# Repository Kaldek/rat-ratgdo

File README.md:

# rat-ratgdo
RAGE
AGAINST
THE
RATGDO

Credit and inspiration for this work goes to [@rlowens](https://github.com/rlowens) to let me know that there are other technical folks out there who needed this other than myself.

## Overview
This is an open source schematic for the ratgdo, based on the v2.5 [ratgdo](https://github.com/PaulWieland/ratgdo) PCB and code but installed using the [ESPHome fork](ESPHome%20vs%20native%20ratgdo.md) of ratgdo.  This project was created to allow people who need a ratgdo solution for their garage door opener but either cannot, or choose not to, source the solution from Paul Wieland. It also ensures that the PCB can be recreated as and when the project maintainer gives up on the project (much like Chamberlain themselves might do with their MyQ Cloud Service) and stops selling PCBs. 

### You are expected to know how to create the described circuit using your own prototyping skills.  That is, this project is for people who can solder well and know how to read schematics

The ***basic*** PCB schematic shown here in the Readme does not describe any circuitry other than the serial line garage door control and obstruction sensor.  All other optional features provided by ratgdo can be reverse engineered as needed, or may already be solved by one of the schematics the community has uploaded!

 As of January 2023, there are now multiple sources for commercially sold ratgdo boards.  **However if you want to buy a pre-made ratgdo setup, we recommend purchasing one [from Paul Wieland](https://github.com/PaulWieland/ratgdo) so as to reward the original creator.**

_Simple basic schematic for a Wemos D1 Mini based module_

See images of a [working breadboard prototype](images/Breadboard_working.png) and the [subsequent soldered prototype using a D1 shield](images/Simple%20prototype%20using%20D1%20shield.jpg).  Both of these prototypes are using 2n7000 MOSFETs exclusively, but that is because they are prototypes and whether a 2n7000 will work for TX will depend greatly on who manufactured your 2n7000.  See the section below on needed components for context.

## Components needed for basic functionality
The basic schematic shown above assumes the use of through-hole components.  If you wish to use SMD components, please refer to the [FAQ](FAQ.md#what-if-i-want-to-use-sot-23-smd-components), and you can also check out the community-provided schematics, which include SMD-based designs.

For this basic design, aside from the obvious requirement of a [supported ESP-32 or ESP8266 board](Supported%20Boards.md) flashed with the [ESPHome version](https://github.com/ratgdo/esphome-ratgdo), you will need:
- 3x 10 kohm (kilo-ohm) resistors
- 1x 2n7000 MOSFET for the RX pin
- 1x AO3400A (soldered to a SOT23 to DIP adapter board) for the TX pin.

It is also recommended you aquire a suitable 3-post screw terminal and some red, white, and black wire for connecting to the door opener.  These connections are very low current, so you can get away with fairly thin wire.

**Note:**  You may **try** to use a 2n7000 MOSFETs for **both** RX and TX, however depending on the manufacturere of your 2n7000 and its production batch, it might not be 100% reliable for the TX circuit because the ~3v switching signal from the ESP8266 may not be enough to trigger the gate of the 2n7000.  There are many examples working using the 2n7000 however, so it might work.  If you have reliability issues for sending commands, we can only recommend you use the AO3400A SMD MOSFET, soldered to a SOT23-to-DIP adapter board.  

## INSTALL REQUIREMENTS
For both this basic schematic shown here in the Readme and how they it is laid out, you must use the ESPHome fork of ratgdo and - for ESP8266 based boards - select the "ratgdo v2.5x" image on the ESPhome [web installer page](https://ratgdo.github.io/esphome-ratgdo/).  For ESP32 based boards the above does not currently apply and you must use the v2.0 installer and follow our basic ESP-32 schematic we provide in the Supported Boards page.

For the ESP8266 based boards, if installing using Paul Wieland's native ratgdo installer and you install for a v2.0 board, you must wire your TX to D4 (GPIO2) rather than D1 (GPIO5).

## Having a PCB printed
You may use the files from the [schematics folder](kicad_files) to have your own PCB printed.  Shown is an example 3D render of an ESP32 based board using a Wemos ESP32 D1 board.

_An example of the D1 Mini ESP32 Wide Format_

Here is an example of a printed PCB with a raw ESP8266 and an LM2596 module, for being powered by a GDO with the battery backup capabilities.

_An example of a PCB using a bare ESP8266 and LM2596 module_

### Schematic options
The community has provided a few options of schematic files suitable for sending to a PCB printing company.
- [Wemos D1 Mini ESP8266](kicad_files/D1%20Mini%20-%20ESP8266)
- [Wemos D1 Mini ESP32](kicad_files/D1%20Mini%20-%20ESP32) (massive overkill for ratgdo but it's your choice!)
- [Wemos D1 Mini ESP32 Wide Format](kicad_files/D1%20Mini%20Wide%20-%20ESP32)
- [Bare ESP8266 module](kicad_files/Bare%20ESP8266)

> If you just want to try ordering a board from somewhere like PCBWay, then check out the most recent [build artifacts](https://github.com/Kaldek/rat-ratgdo/actions/workflows/pcb.yaml)

## How the ratgdo circuit works
The ratgdo circuitry which we cover in this project consists of two sections; Garage Door control and obstruction sensors.

### Garage Door Control
#### Description of the Chamberlain configuration
The Chamberlain garage door control circuit is a two-wire setup consisting of a Ground, and a combined +12v power and serial data line.  The serial data line is held at 12v unless data transmission is occurring.  Data transmission is performed by pulling the 12v line down to GND for each data bit.  The benefit here is that a single wire can be used for providing power to door control panels and data transmssion on a single wire.  The use of appropriately sized capacitors in door control panels means they do not switch off during data transmission.

#### How ratgdo interfaces with the Chamberlain wiring
The ratgdo taps into the red control wire and uses this single wire for transmission of commands onto the serial bus, and for receiving data from the serial bus.  As it is a single wire protocol and operates half-duplex, the ratgdo circuitry uses N-channel MOSFETs wired in a manner which allows the ESP8266 to never transmit when the serial line is already low.

In operation, this means that the ratgdo is mostly listening to the serial bus to ensure it is keeping track of the state of the door.  For example, if the door is manually opened (or opened by use of the MyQ app even), these events are broadcast onto the serial bus by the door controller.  ratgdo is therefore able to know that the state of the door has changed.  In turn, this means that when controlling ratgdo via Home Assistant, the status of the door in HA is always up to date.

#### Wiring to Garage Door

### Obstruction sensor
The ratgdo monitors the real-time state of the obstruction sensors directly.  We assume this is because obstruction status is not broadcast in real time by the door controller, and safety is paramount.  It allows you to set up real-time alerts in Home Assistant for any time the door is obstructed.  The ratgdo taps into the obstruction sensor power wire which also acts as a communication bus, however the signalling is only an ongoing status of whether the obstruction sensors are working and whether there is an obstruction.

## Contributing
This is a fully open repo, in that we welcome any and all additions for all sorts of Edge Cases.  If you come up with something and would like it to be available to the community, raise a Pull Request and we'll work with you to get it published!

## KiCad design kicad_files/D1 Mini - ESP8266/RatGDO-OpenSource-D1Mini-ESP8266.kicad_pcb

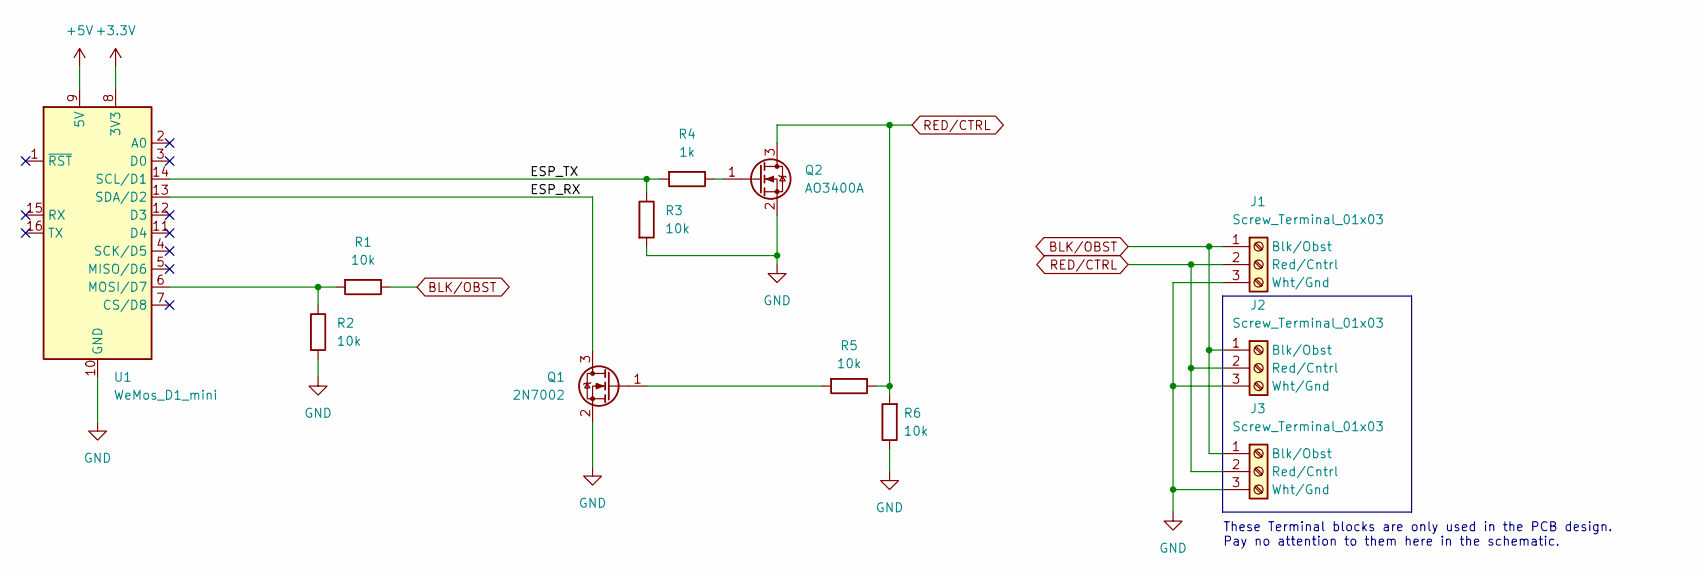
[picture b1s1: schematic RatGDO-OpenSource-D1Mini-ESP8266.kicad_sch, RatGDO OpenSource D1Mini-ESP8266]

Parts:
J1: Screw_Terminal_01x03; TerminalBlock_Phoenix_MKDS-1,5-3_1x03_P5.00mm_Horizontal
J2: Screw_Terminal_01x03; PhoenixContact_MCV_1,5_3-G-3.5_1x03_P3.50mm_Vertical
J3: Screw_Terminal_01x03; PinHeader_1x03_P2.54mm_Vertical
Q1: 2N7002; SOT-23_Handsoldering
Q2: AO3400A; SOT-23_Handsoldering
R1, R2, R3, R5, R6: 10k; R_0805_2012Metric_Pad1.20x1.40mm_HandSolder
R4: 1k; R_0805_2012Metric_Pad1.20x1.40mm_HandSolder
U1: WeMos_D1_mini; WEMOS_D1_mini_light

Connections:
+3.3V: U1.8 (3V3)
+5V: U1.9 (5V)
/ESP_RX: Q1.3 (D), U1.13 (SDA/D2)
/ESP_TX: R3.1, R4.2, U1.14 (SCL/D1)
BLK/OBST: J1.1 (Blk/Obst), J2.1 (Blk/Obst), J3.1 (Blk/Obst), R1.1
GND: J1.3 (Wht/Gnd), J2.3 (Wht/Gnd), J3.3 (Wht/Gnd), Q1.2 (S), Q2.2 (S), R2.2, R3.2, R6.1, U1.10 (GND)
unnamed: Q1.1 (G), R5.2
unnamed: Q2.1 (G), R4.1
unnamed: R1.2, R2.1, U1.6 (MOSI/D7)
RED/CTRL: J1.2 (Red/Cntrl), J2.2 (Red/Cntrl), J3.2 (Red/Cntrl), Q2.3 (D), R5.1, R6.2

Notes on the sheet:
These Terminal blocks are only used in the PCB design. Pay no attention to them here in the schematic.

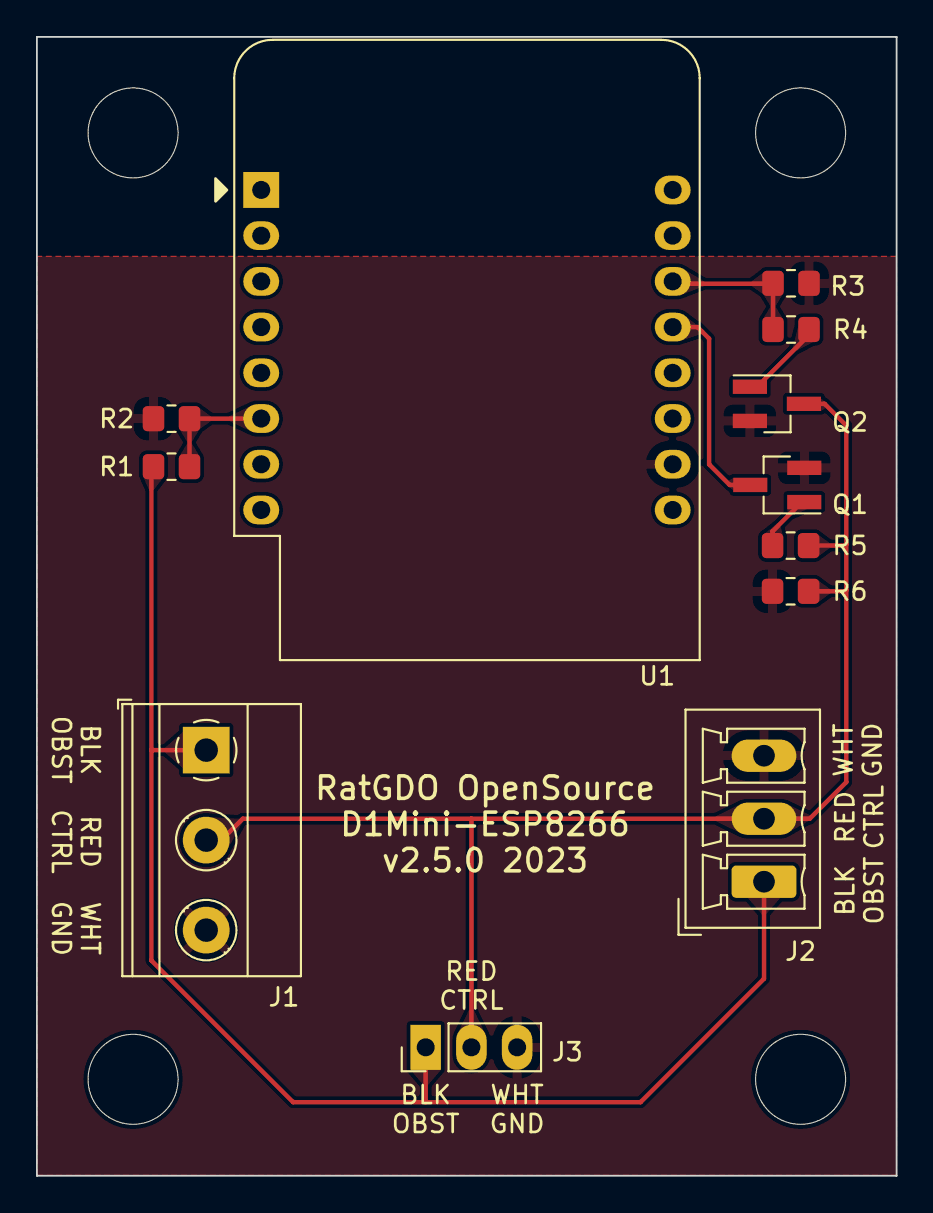
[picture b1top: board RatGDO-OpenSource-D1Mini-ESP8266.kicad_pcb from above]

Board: 2 copper layers, 47.8 x 63.3 mm, 16 parts (0 on the bottom side), 8 nets.

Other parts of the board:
H1, H1#2, H1#3, H1#4: MountingHole_5mm

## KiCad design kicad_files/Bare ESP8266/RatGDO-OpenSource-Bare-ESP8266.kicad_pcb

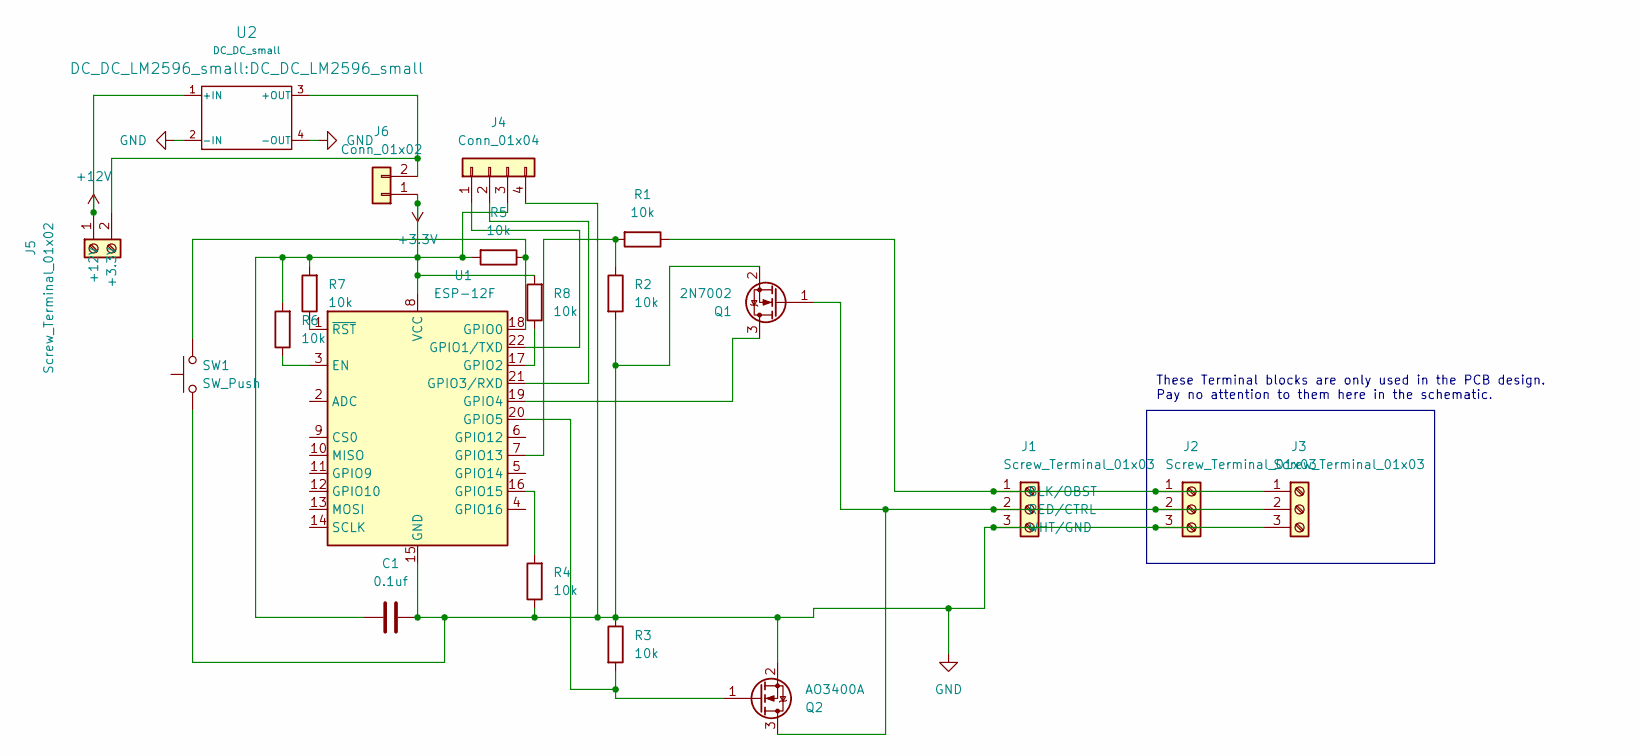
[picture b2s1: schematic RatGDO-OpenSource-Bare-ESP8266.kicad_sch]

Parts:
C1: 0.1uf; C_0805_2012Metric
J1: Screw_Terminal_01x03; TerminalBlock_Phoenix_MKDS-1,5-3_1x03_P5.00mm_Horizontal
J2: Screw_Terminal_01x03; PhoenixContact_MCV_1,5_3-G-3.5_1x03_P3.50mm_Vertical
J3: Screw_Terminal_01x03; PinSocket_1x03_P2.54mm_Vertical
J4: Conn_01x04; PinSocket_1x04_P2.54mm_Vertical
J5: Screw_Terminal_01x02; TerminalBlock_Phoenix_MKDS-1,5-2_1x02_P5.00mm_Horizontal
J6: Conn_01x02; PinHeader_1x02_P2.54mm_Vertical
Q1: 2N7002; SOT-23
Q2: AO3400A; SOT-23
R1, R2, R3, R4, R5, R6, R7, R8: 10k; R_0805_2012Metric
SW1: SW_Push; SW_SPST_EVQQ2
U1: ESP-12F; ESP-12E
U2: DC_DC_small; DC_DC_LM2596_small

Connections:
+3.3V: C1.1, J4.3, J6.1, R5.2, R6.2, R7.2, R8.2, U1.8 (VCC)
+12V: J5.1 (+12V), U2.1 (+IN)
GND: C1.2, J1.3 (WHT/GND), J2.3, J3.3, J4.4, Q1.2 (S), Q2.2 (S), R2.2, R3.1, R4.1, SW1.1, U1.15 (GND), U2.2 (-IN), U2.4 (-OUT)
unnamed: J1.1 (BLK/OBST), J2.1, J3.1, R1.1
unnamed: J1.2 (RED/CTRL), J2.2, J3.2, Q1.1 (G), Q2.3 (D)
unnamed: J4.1, U1.22 (GPIO1/TXD)
unnamed: J4.2, U1.21 (GPIO3/RXD)
unnamed: J5.2 (+3.3V), J6.2, U2.3 (+OUT)
unnamed: Q1.3 (D), U1.19 (GPIO4)
unnamed: Q2.1 (G), R3.2, U1.20 (GPIO5)
unnamed: R6.1, U1.3 (EN)
unnamed: R5.1, SW1.2, U1.18 (GPIO0)
unnamed: R8.1, U1.17 (GPIO2)
unnamed: R1.2, R2.1, U1.7 (GPIO13)
unnamed: R4.2, U1.16 (GPIO15)
unnamed: R7.1, U1.1 (~RST)

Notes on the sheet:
These Terminal blocks are only used in the PCB design. Pay no attention to them here in the schematic.

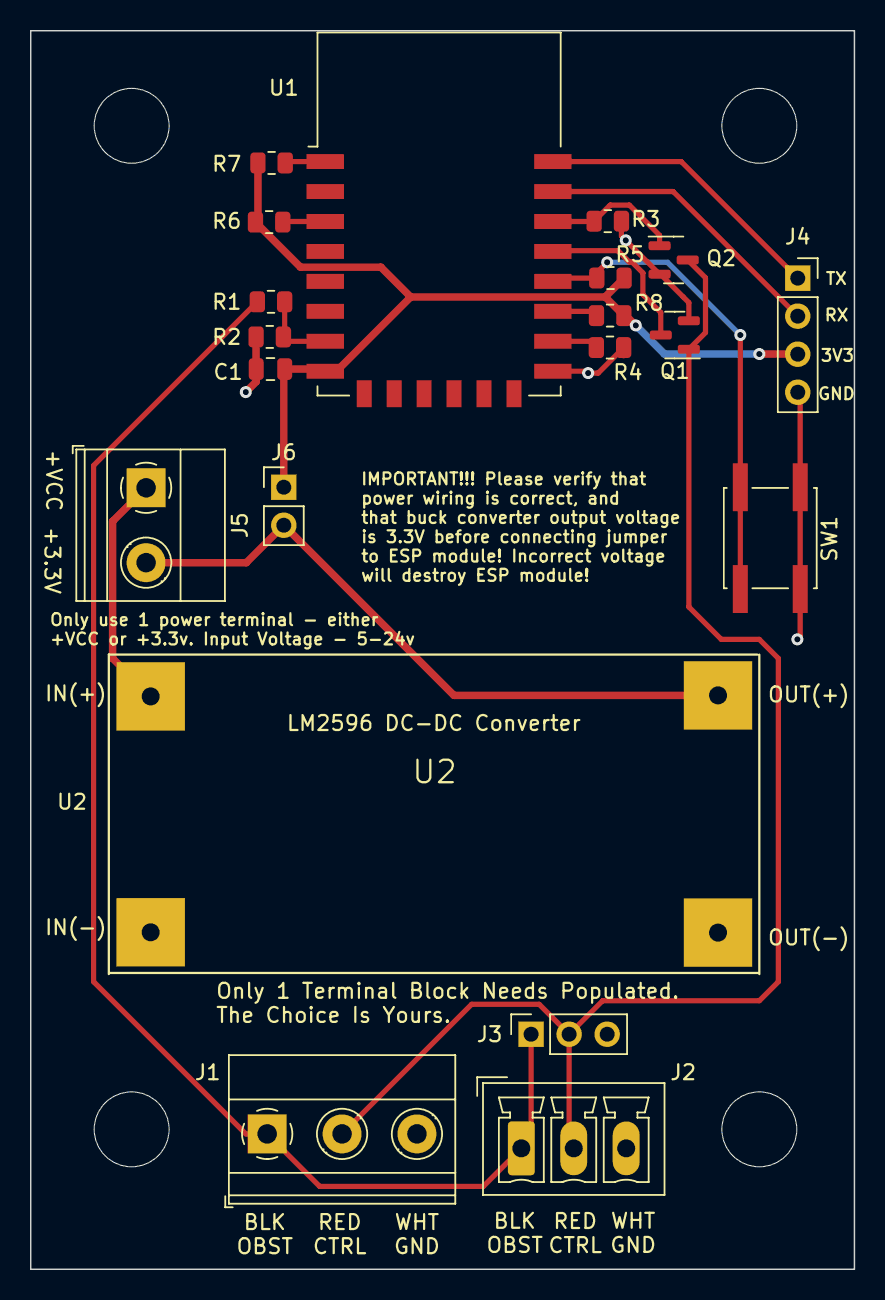
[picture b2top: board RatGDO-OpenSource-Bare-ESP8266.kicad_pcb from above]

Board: 2 copper layers, 55.0 x 82.7 mm, 24 parts (0 on the bottom side), 16 nets.

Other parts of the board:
H1, H1#2, H1#3, H1#4: MountingHole_5mm

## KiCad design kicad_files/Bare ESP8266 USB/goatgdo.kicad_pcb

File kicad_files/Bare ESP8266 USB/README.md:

# ESP8266 12-F USB-C KiCad files

A reworking of the Bare ESP8266 board design that uses USB-C for power instead of an LM2596 submodule, and uses just one GDO connector header to allow for a smaller board footprint.

Compatable with RatGDO ESPHome software for the v2.5 official board.

## Populating

Populating the Flash switch, Reset switch, and ICSP header are optional, but will make first time programming easier.

## Powering 

This board uses a 6-pin power-only USB-C jack that can be either hand soldered or paste reflowed. It's a normal 5V USB sink device, so any "dumb" USB wall-wart can be used.

It can also be powered via the 3.3V pin of the ICSP header - there's no need to connect USB while serial programming it.

If you wish to power the device directly from the programming header using 3.3V, you can skip populating the USB-C port, resistors R2 and R3, and the LDO regulator CR1, but you should ensure you're using a stable and regulated 3.3V supply.

If your GDO has battery backup system, I'd recommend using one of the LM2996 module based boards in this repository instead of this one.

## Programming

The USB-C port on this board is for power only - you need to use the ICSP programming header with a seperate TTL-level RS232 programming interface to load the initial firmware.

The ICSP header will mate directly with the 
[SparkFun Serial Basic Breakout](https://www.sparkfun.com/products/14050) for programming, but any 3.3V RS232 interface can be used by connecting TX, RX, VCC and GND appropriately.

Auto reset via serial hardware control lines isn't supported - you'll need to press the Reset button manually after programming, or power cycle the device.

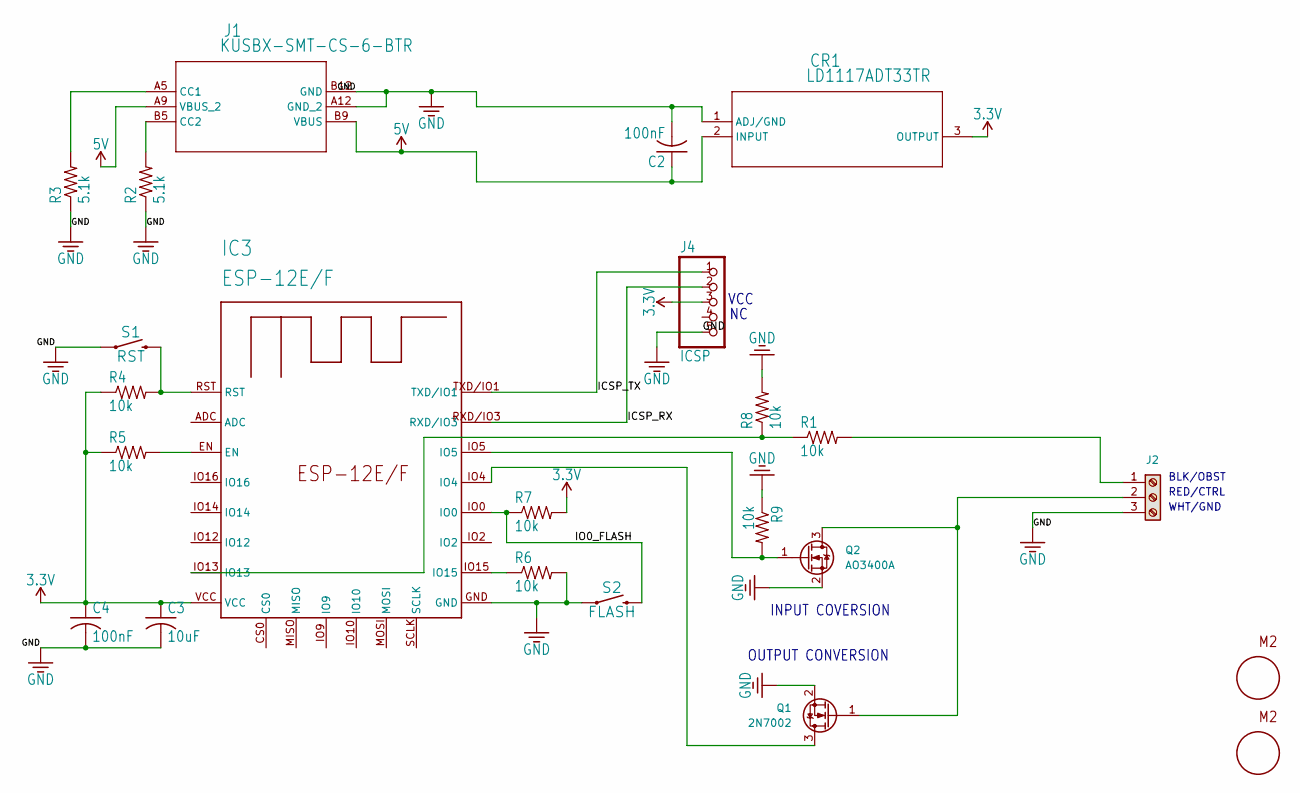
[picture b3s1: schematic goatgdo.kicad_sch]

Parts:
C2, C4: 100nF; C0805
C3: 10uF; C0805
CR1: LD1117ADT33TR; DPAK_STM
IC3: ESP-12E/F; ESP-12E
J1: KUSBX-SMT-CS-6-BTR; KUSBX-SMT-CS-6-BTR_KYC
J2: Screw_Terminal_01x03; TerminalBlock_MetzConnect_Type011_RT05503HBWC_1x03_P5.00mm_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
J4: ICSP; 1X05
Q1: 2N7002; SOT-23_Handsoldering
Q2: AO3400A; SOT-23_Handsoldering
R1, R4, R5, R6, R7, R8, R9: 10k; R0805
R2, R3: 5.1k; R0805
S1: RST; TACTILE_SWITCH_PTH_6.0MM
S2: FLASH; TACTILE_SWITCH_PTH_6.0MM
U$4, U$6: M2-POST

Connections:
3.3V: C3.1, C4.1, CR1.3 (OUTPUT), IC3.VCC, J4.3, R4.1, R5.1, R7.2
5V: C2.1, CR1.2 (INPUT), J1.A9 (VBUS_2), J1.B9 (VBUS)
/ICSP_RX: IC3.RXD/IO3, J4.2
/ICSP_TX: IC3.TXD/IO1, J4.1
/IO0_FLASH: IC3.IO0, R7.1, S2.3 (2)
GND: C2.2, C3.2, C4.2, CR1.1 (ADJ/GND), IC3.GND, J1.A12 (GND_2), J1.B12 (GND), J2.3, J4.5, Q1.2 (S), Q2.2 (S), R2.1, R3.1, R6.2, R8.2, R9.1, S1.1, S2.1
unnamed: IC3.EN, R5.2
unnamed: IC3.IO13, R1.1, R8.1
unnamed: IC3.IO15, R6.1
unnamed: J1.A5 (CC1), R3.2
unnamed: J1.B5 (CC2), R2.2
unnamed: J2.1, R1.2
unnamed: J2.2, Q1.1 (G), Q2.3 (D)
unnamed: IC3.IO4, Q1.3 (D)
unnamed: IC3.IO5, Q2.1 (G), R9.2
unnamed: IC3.RST, R4.2, S1.3 (2)

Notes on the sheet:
INPUT COVERSION
BLK/OBST
WHT/GND
OUTPUT CONVERSION
RED/CTRL
VCC

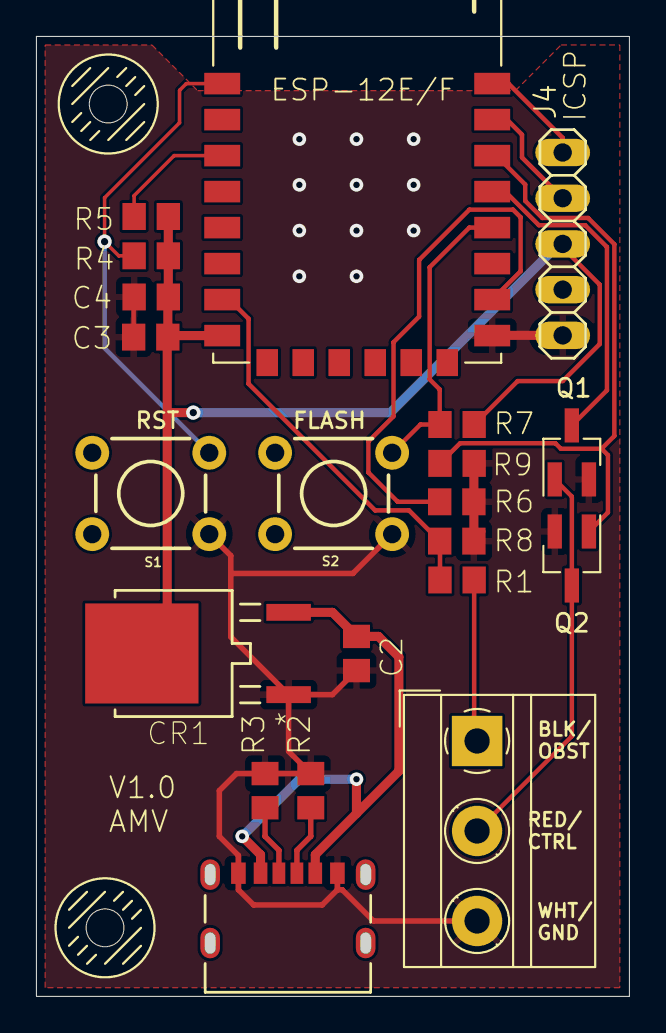
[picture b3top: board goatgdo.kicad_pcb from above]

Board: 2 copper layers, 32.4 x 52.8 mm, 23 parts (0 on the bottom side), 16 nets.

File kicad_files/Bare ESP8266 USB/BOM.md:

## BOM

|Part 	|Qty 	|Value 	|Reference 	|Link 	|
|-|-|-|-|-|
|0805 Resistor 				|7 	|10k 	|R1, R4, R5, R6, R7, R8, R9 	|																											|
|0805 Resistor 				|2 	|5.1k 	|R2, R3 						|																											|
|0805 Capacitor				|2 	|100nF 	|C2, C4 						|																											|
|0805 Capacitor				|1 	|10uF	|C3 							| 																											|
|Switch (Optinal) 			|2 	| 		|S1 (Rst), S2 (Flash)			|[Digikey](https://www.digikey.com/en/products/detail/cui-devices/TS02-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 		|
|2N7002 					|1 	| 		|Q1 							|[Digikey](https://www.digikey.com/en/products/detail/onsemi/2N7002/244345) 								|
|AO3400A 					|1 	| 		|Q2 							|[Digikey](https://www.digikey.com/en/products/detail/alpha-omega-semic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	|
|2.54mm header (Optional)	|1 	| 		|J4 (ICSP)						| 																											|
|1x3 Screw Term				|1 	|		|J2	(GDO)						|[Digikey](https://www.digikey.com/en/products/detail/phoenix-contact/1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						|
|3.3V LDO Regulator			|1 	|LD1117 |CR1 							|[Digikey](https://www.digikey.com/en/products/detail/stmicroelectronic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 				|
|ESP8266 12F 				|1 	|		|IC3 							|[Amazon](https://www.amazon.com/gp/product/B089PTN2V5/) 													|
|USB-C Connector			|1 	|		|J1 							|[Digikey](https://www.digikey.com/en/products/detail/kycon-inc/KUSBX-S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				|

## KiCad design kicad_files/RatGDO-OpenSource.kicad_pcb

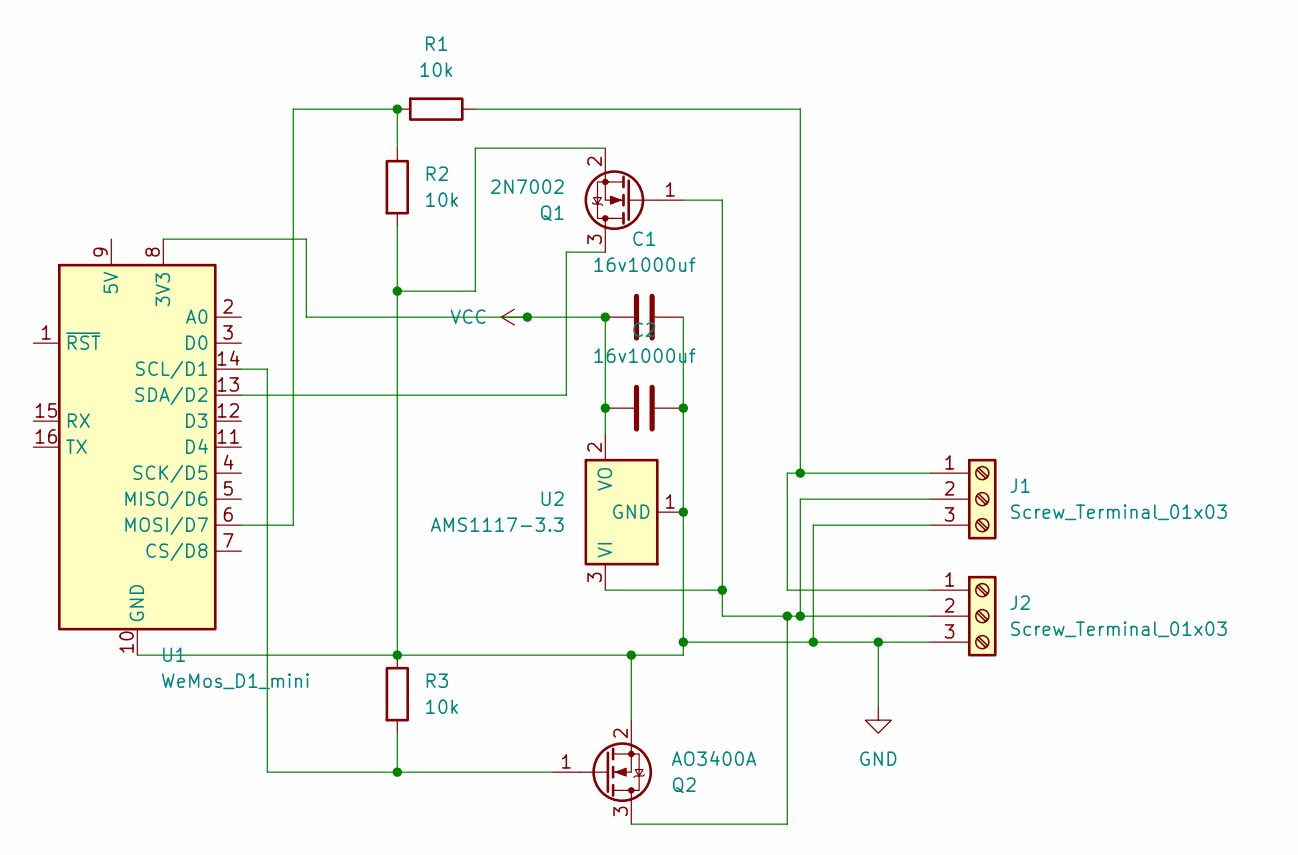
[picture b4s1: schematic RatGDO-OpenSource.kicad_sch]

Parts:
C1: 16v1000uf; CP_Elec_10x10.5
C2: 16v1000uf; CP_Radial_D10.0mm_P5.00mm
J1: Screw_Terminal_01x03; TerminalBlock_Phoenix_MKDS-1,5-3_1x03_P5.00mm_Horizontal
J2: Screw_Terminal_01x03; PhoenixContact_MCV_1,5_3-G-3.5_1x03_P3.50mm_Vertical
Q1: 2N7002; SOT-23
Q2: AO3400A; SOT-23
R1, R2, R3: 10k; R_0805_2012Metric
U1: WeMos_D1_mini; WEMOS_D1_mini_light
U2: AMS1117-3.3; SOT-223-3_TabPin2

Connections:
GND: C1.2, C2.2, J1.3, J2.3, Q1.2 (S), Q2.2 (S), R2.2, R3.1, U1.10 (GND), U2.1 (GND)
unnamed: J1.1, J2.1, R1.1
unnamed: J1.2, J2.2, Q1.1 (G), Q2.3 (D), U2.3 (VI)
unnamed: Q1.3 (D), U1.13 (SDA/D2)
unnamed: Q2.1 (G), R3.2, U1.14 (SCL/D1)
unnamed: R1.2, R2.1, U1.6 (MOSI/D7)
VCC: C1.1, C2.1, U1.8 (3V3), U2.2 (VO)

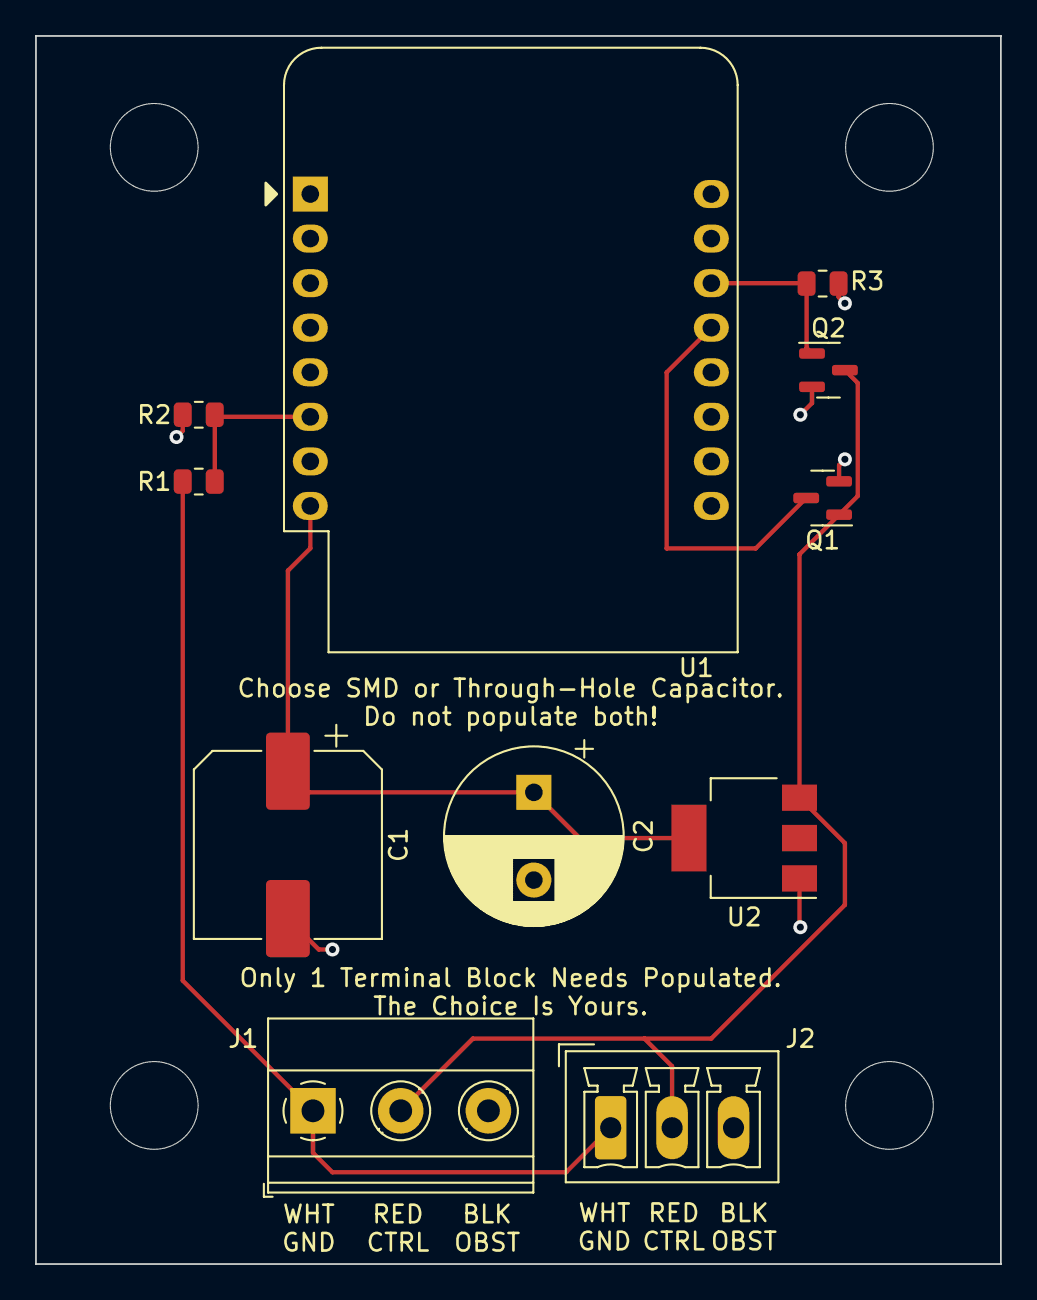
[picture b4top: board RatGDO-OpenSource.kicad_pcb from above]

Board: 2 copper layers, 55.0 x 70.0 mm, 11 parts (0 on the bottom side), 7 nets.

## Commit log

2023-10-25 Better MOSFET recommendations
    Due to switching voltage of ESP8266 (3.3v) the IRLB8721 is a better recommendation when using through-hole designs.
2023-10-25 Updated schematic using IRLB8721 MOSFET for TX
    TX should use a MOSFET which will more reliably switch with 3.3v logic.
2023-10-25 Changed schematic diagram insert to use v2 diagram
2023-10-25 Added recommendations for Surface Mount (SMD) MOSFETs.
2023-10-25 v3 Diagram as Fritzing has S/G/G wrong
    MOSFET layout for Source/Gate/Drain in Fritzing is apparently wrong. Adding S/G/D labels for clarity.
2023-10-25 Updated diagram to v3
    Fritzing appears to be stuffing up the Source/Gate/Drain pin numbering of MOSFET icons so we added S/G/D labels.
2023-10-25 Delete ratgdo open source_schem.png
    Removed due to recommendation of MOSFETs wrong.
2023-10-25 Removed due to S/G/D labelling issues from Fritzing
2023-10-25 Added notes about why we use D1
    D1 (GPIO5) is used for TX as per ratgdo v2.5 boards which the ESPHome version is now using for flashing.
2023-10-25 Confirmed this design is using code for board rev 2.5
    As of ratgdo board revision 2.5 the code now uses D1 (GPIO5) for TX. This PCB design expected to use that code.
2023-10-25 Clarified which installers to use
    ESPHome Web installer allows for installation to v1.0, 2.0 and v2.5 boards. The schematic shown is based on the v2.5 board layout. Use of Paul Wieland's installer only supports v2.0 boards currently 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
2023-10-25 Schematics for v2.5 boards using Ki-Cad
2023-10-25 Replaced diagrams with Ki-Cad version
    No longer using Baby's First PCB Fesigner (aka Fritzing).
2023-10-25 Deleting crappy diagrams that used Fritzing.
2023-10-25 Linked to FAQ
2023-10-25 Added mention of SMD resistors.
2023-10-25 Ki-cad file was wrong.
2023-10-25 Clarified that the design assumes use of a D1 Mini rather than raw ESP8266
2023-10-25 Uploaded diagram with proper MOSFET S/G/D orientation
2023-10-25 Added image of breadboard for evidence of working prototype
2023-10-25 Clarified this schematic assumes use of D1 Mini.
2023-10-25 Clarity changes in overview.
2023-10-25 Fixed typo.
2023-10-25 Added reasoning why there are different MOSFETs.
2023-10-26 Added image of soldered prototype.
2023-10-26 Added 10k resistor to Obst. circuit as this is a voltage divider
2023-10-26 Add reference to voltage divider in obstruction detection circuit.
2023-10-26 Fixed stupid wire routing in diagram
    Diagram v5 had the Drain of the TX MOSFET connected to Ground rather than the Red Wire.
2023-10-26 Deleted v5 diagram as routing is wrong.
2023-10-28 v6 diagram still had stupid Fritzing GND routing wrong.
2023-10-28 Delete original breadboard image
    Breadboard original image missing 10k resistor on obstruction wire for voltage divider.
2023-10-28 Adding KiCAD Files and gerber files for review.
2023-10-28 Updated Files to match new Schematics
2023-10-29 Remove power supply components
2023-10-29 Added gitignore
2023-10-29 Added .lck files to gitignore
2023-10-30 Update Using red wire for power.md
    Alternate option to power the ESP from the backup battery connector
2023-10-30 Update to recommend use of battery backup for power
2023-10-30 Removed references to using red wire for power successfully.
2023-10-30 Add notes on potential different wire colours
2023-10-31 Redid folder structure and setup folders for different modules
    Redid folder structure
    Added folders and projects for D1 minis in the ESP32 and ESP8266 varieties
2023-10-31 Handling Merge conflicts
2023-10-31 Forcing old files to delete
2023-10-31 Fixed Bad PCB Labeling
2023-10-31 Force Recreate of Gerber files
2023-10-31 Change Pin Header to Pin Socket
2023-10-31 Cleaning up Schematics and making PCB layout similar for D1 Boards
2023-10-31 Updating BOM Files for D1 Mini-8266
2023-11-01 Remove recommendation of IRLB8721
    Removed recommendation to use IRLB8721 and replaced with RFP30N06LE. We know the latter works and we have seen issues with the former.
2023-11-01 Replaced image with schematic using RFP30N06LE
    Removal of IRLB8721 and replacement with RFP30N06LE.
2023-11-01 Changed TX MOSFET to RFP30n06le
2023-11-03 Blinking warning
2023-11-04 added new images and updated readme
2023-11-04 added info about process
2023-11-04 fixed img links
2023-11-07 Added Bare ESP8266 kicad files.
2023-11-08 Missed Silkscreening for programming header
2023-11-08 Updated Trace widths
2023-11-08 Missed saving a changed file
2023-11-08 Added silkscreen to LM2596 area to aid in placement.
2023-11-10 ESP32 footprint did not properly create a keepout zone.
2023-11-10 ESP8266 footprint did not properly create a keepout zone.
2023-11-11 Add new wide board format for D1 Mini ESP32
2023-11-11 Add workflows
2023-11-12 Add 3D render example of the open source schematic
2023-11-14 Cleanup files for gerber builds
2023-11-17 Fixed Silkscreen issue - positive and ground swap
2023-11-21 Added image of printed PCB
2023-11-21 Made PCB image viewable inline.
2023-11-24 Replaced Fritzing Schematic
2023-11-24 Update ESP8266 schematics and PCB
    Added 1K R4 on gate of Q2.
    Added 10K R5/R6 on gate of Q1.
    Re-laid out PCB, all single sided and smaller.
2023-11-24 Update ESP32 Mini schematics and PCB
    Added 1K R4 on gate of Q2.
    Added 10K R5/R6 on gate of Q1.
    Re-laid out PCB, all single sided and smaller.
    Changed pads to hand solder.
    Modified from ESP8266 layout.
2023-12-18 Update ESPHome vs native ratgdo.md
    Minor MarkDown adjustment for avahi link
2023-12-25 Add config for 4MB flash support
2023-12-25 Fixed typo and added context for 4MB flash support
2023-12-29 Added support for modules with 2MB flash.
2023-12-29 Update ESPHome vs native ratgdo.md
    Clarified that the YAML for supporting 2MB flash is to be added to the ESPHome dashboard when configuring a device.
2023-12-29 Updated and added references to the esphome-ratgdo support for 4MB already
2024-01-11 Added KiCad Project
2024-01-25 Update to reflect current state of ratgdo commercial options.
2024-06-18 Updated references to which web installer option to use.
2024-06-30 Adding TX mapping for ESP-WROOM-32
2024-09-05 Changed TX MOSFET recommendation to just use AO3400A
2024-09-05 Added even more wording to make it clear the 2n7000 for TX is a roll of the dice.
